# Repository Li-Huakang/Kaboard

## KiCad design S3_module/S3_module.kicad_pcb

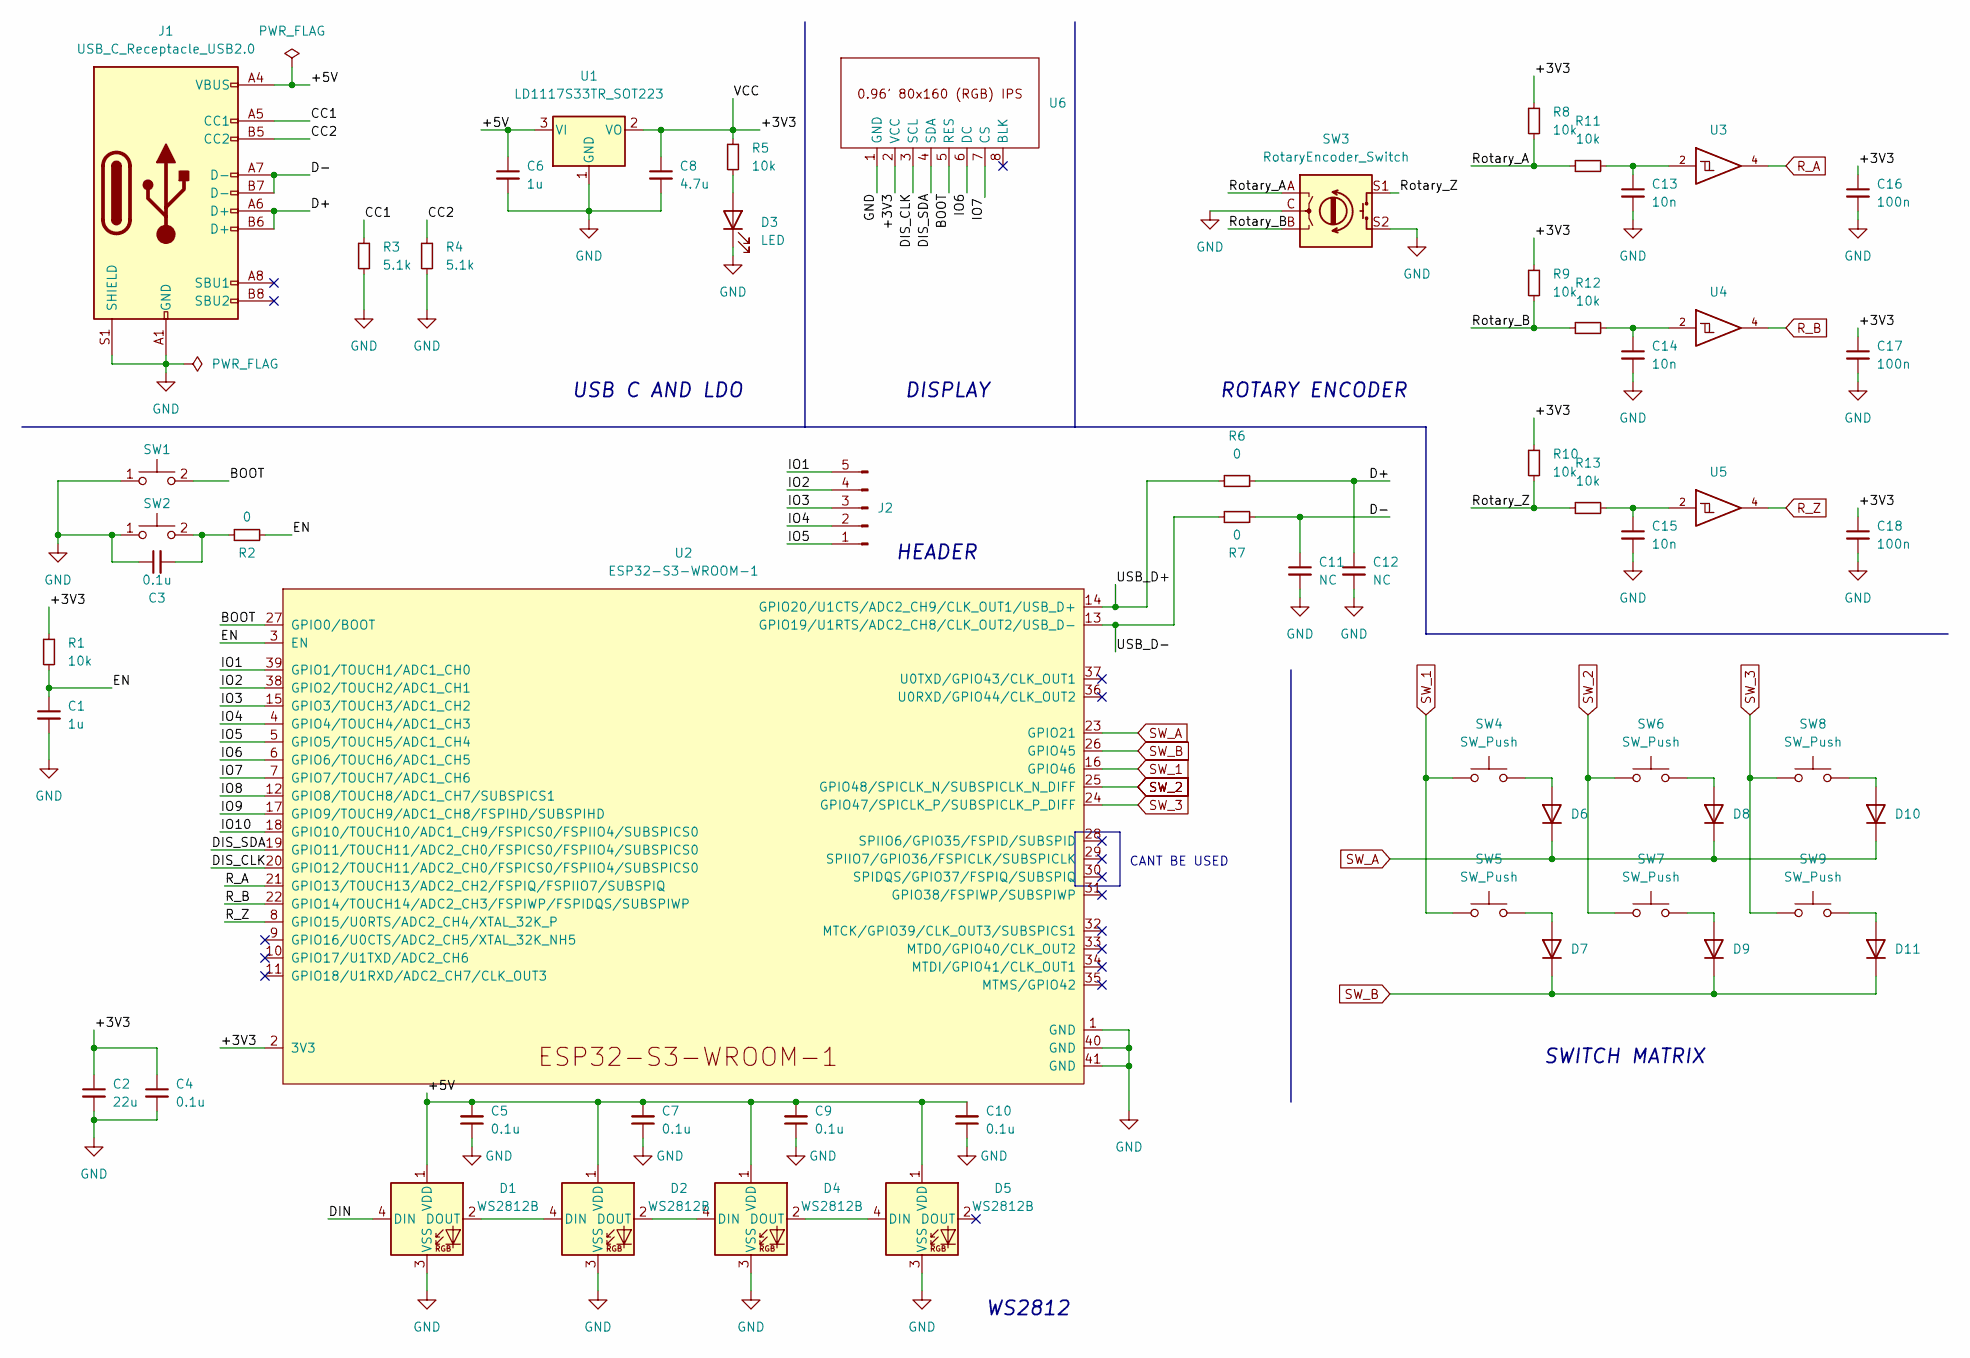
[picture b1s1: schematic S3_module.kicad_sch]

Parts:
C1, C6: 1u; C_0805_2012Metric_Pad1.18x1.45mm_HandSolder
C2: 22u; C_0805_2012Metric_Pad1.18x1.45mm_HandSolder
C3, C4, C5, C7, C9, C10: 0.1u; C_0805_2012Metric_Pad1.18x1.45mm_HandSolder
C8: 4.7u; C_0805_2012Metric_Pad1.18x1.45mm_HandSolder
C11, C12: NC; C_0805_2012Metric_Pad1.18x1.45mm_HandSolder
C13, C14, C15: 10n; C_0805_2012Metric_Pad1.18x1.45mm_HandSolder
C16, C17, C18: 100n; C_0805_2012Metric_Pad1.18x1.45mm_HandSolder
D1, D2, D4, D5: WS2812B; LED_WS2812B_PLCC4_5.0x5.0mm_P3.2mm
D3: LED; LED_0805_2012Metric_Pad1.15x1.40mm_HandSolder
D6, D7, D8, D9, D10, D11: 1N4148WS; D_SOD-323
J1: USB_C_Receptacle_USB2.0; USB_C_Receptacle_HRO_TYPE-C-31-M-12
J2: Conn_01x05_Male; PinHeader_1x05_P2.54mm_Vertical
R1, R5, R8, R9, R10, R11, R12, R13: 10k; R_0805_2012Metric_Pad1.20x1.40mm_HandSolder
R2, R6, R7: 0; R_0805_2012Metric_Pad1.20x1.40mm_HandSolder
R3, R4: 5.1k; R_0805_2012Metric_Pad1.20x1.40mm_HandSolder
SW1, SW2: (no value)
SW3: RotaryEncoder_Switch; RotaryEncoder_Alps_EC11E-Switch_Vertical_H20mm
SW4, SW5, SW6, SW7, SW8, SW9: SW_Push; SW_Cherry_MX_Plate_1.00u
U1: LD1117S33TR_SOT223; SOT-223-3_TabPin2
U2: ESP32-S3-WROOM-1
U3, U4, U5: 74LVC1G17; SOT-353_SC-70-5_Handsoldering
U6: 0.96_80x160_IPS

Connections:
/+5V: C5.2, C6.1, C7.2, C9.2, C10.2, D1.1 (VDD), D2.1 (VDD), D4.1 (VDD), D5.1 (VDD), J1.A4 (VBUS), J1.A9 (VBUS), J1.B4 (VBUS), J1.B9 (VBUS), U1.3 (VI)
/BOOT: SW1.2, U2.27 (GPIO0/BOOT), U6.5 (RES)
/CC1: J1.A5 (CC1), R3.1
/CC2: J1.B5 (CC2), R4.1
/D+: C12.1, J1.A6 (D+), J1.B6 (D+), R6.1
/D-: C11.1, J1.A7 (D-), J1.B7 (D-), R7.1
/DIN: D1.4 (DIN)
/DIS_CLK: U2.20 (GPIO12/TOUCH11/ADC2_CH0/FSPICS0/FSPIIO4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), U6.3 (SCL)
/DIS_SDA: U2.19 (GPIO11/TOUCH11/ADC2_CH0/FSPICS0/FSPIIO4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), U6.4 (SDA)
/EN: C1.1, R1.2, R2.2, U2.3 (EN)
/IO1: J2.5, U2.39 (GPIO1/TOUCH1/ADC1_CH0)
/IO2: J2.4, U2.38 (GPIO2/TOUCH2/ADC1_CH1)
/IO3: J2.3, U2.15 (GPIO3/TOUCH3/ADC1_CH2)
/IO4: J2.2, U2.4 (GPIO4/TOUCH4/ADC1_CH3)
/IO5: J2.1, U2.5 (GPIO5/TOUCH5/ADC1_CH4)
/IO6: U2.6 (GPIO6/TOUCH6/ADC1_CH5), U6.6 (DC)
/IO7: U2.7 (GPIO7/TOUCH7/ADC1_CH6), U6.7 (CS)
/IO8: U2.12 (GPIO8/TOUCH8/ADC1_CH7/SUBSPICS1)
/IO9: U2.17 (GPIO9/TOUCH9/ADC1_CH8/FSPIHD/SUBSPIHD)
/IO10: U2.18 (GPIO10/TOUCH10/ADC1_CH9/FSPICS0/FSPIIO4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)
/Rotary_A: R8.2, R11.1, SW3.A
/Rotary_B: R9.2, R12.1, SW3.B
/Rotary_Z: R10.2, R13.1, SW3.S1
/USB_D+: R6.2, U2.14 (GPIO20/U1CTS/ADC2_CH9/CLK_OUT1/USB_D+)
/USB_D-: R7.2, U2.13 (GPIO19/U1RTS/ADC2_CH8/CLK_OUT2/USB_D-)
GND: C1.2, C2.2, C3.1, C4.2, C5.1, C6.2, C7.1, C8.2, C9.1, C10.1, C11.2, C12.2, C13.2, C14.2, C15.2, C16.2, C17.2, C18.2, D1.3 (VSS), D2.3 (VSS), D3.1 (K), D4.3 (VSS), D5.3 (VSS), J1.A1 (GND), J1.A12 (GND), J1.B1 (GND), J1.B12 (GND), J1.S1 (SHIELD), R3.2, R4.2, SW1.1, SW2.1, SW3.C, SW3.S2, U1.1 (GND), U2.1 (GND), U2.40 (GND), U2.41 (GND), U3.3 (GND), U4.3 (GND), U5.3 (GND), U6.1 (GND)
unnamed: C3.2, R2.1, SW2.2
unnamed: C13.1, R11.2, U3.2
unnamed: C14.1, R12.2, U4.2
unnamed: C15.1, R13.2, U5.2
unnamed: D1.2 (DOUT), D2.4 (DIN)
unnamed: D2.2 (DOUT), D4.4 (DIN)
unnamed: D3.2 (A), R5.2
unnamed: D4.2 (DOUT), D5.4 (DIN)
unnamed: D6.2 (A), SW4.2
unnamed: D7.2 (A), SW5.2
unnamed: D8.2 (A), SW6.2
unnamed: D9.2 (A), SW7.2
unnamed: D10.2 (A), SW8.2
unnamed: D11.2 (A), SW9.2
R_A: U2.21 (GPIO13/TOUCH13/ADC2_CH2/FSPIQ/FSPIIO7/S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), U3.4
R_B: U2.22 (GPIO14/TOUCH14/ADC2_CH3/FSPIWP/FSPIDQS/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), U4.4
R_Z: U2.8 (GPIO15/U0RTS/ADC2_CH4/XTAL_32K_P), U5.4
SW_1: SW4.1, SW5.1, U2.16 (GPIO46)
SW_2: SW6.1, SW7.1, U2.25 (GPIO48/SPICLK_N/SUBSPICLK_N_DIFF)
SW_3: SW8.1, SW9.1, U2.24 (GPIO47/SPICLK_P/SUBSPICLK_P_DIFF)
SW_A: D6.1 (K), D8.1 (K), D10.1 (K), U2.23 (GPIO21)
SW_B: D7.1 (K), D9.1 (K), D11.1 (K), U2.26 (GPIO45)
VCC: C2.1, C4.1, C8.1, C16.1, C17.1, C18.1, R1.1, R5.1, R8.1, R9.1, R10.1, U1.2 (VO), U2.2 (3V3), U3.5 (VCC), U4.5 (VCC), U5.5 (VCC), U6.2 (VCC)

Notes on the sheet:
CANT BE USED
SWITCH MATRIX
USB C AND LDO
ROTARY ENCODER
DISPLAY
HEADER
WS2812

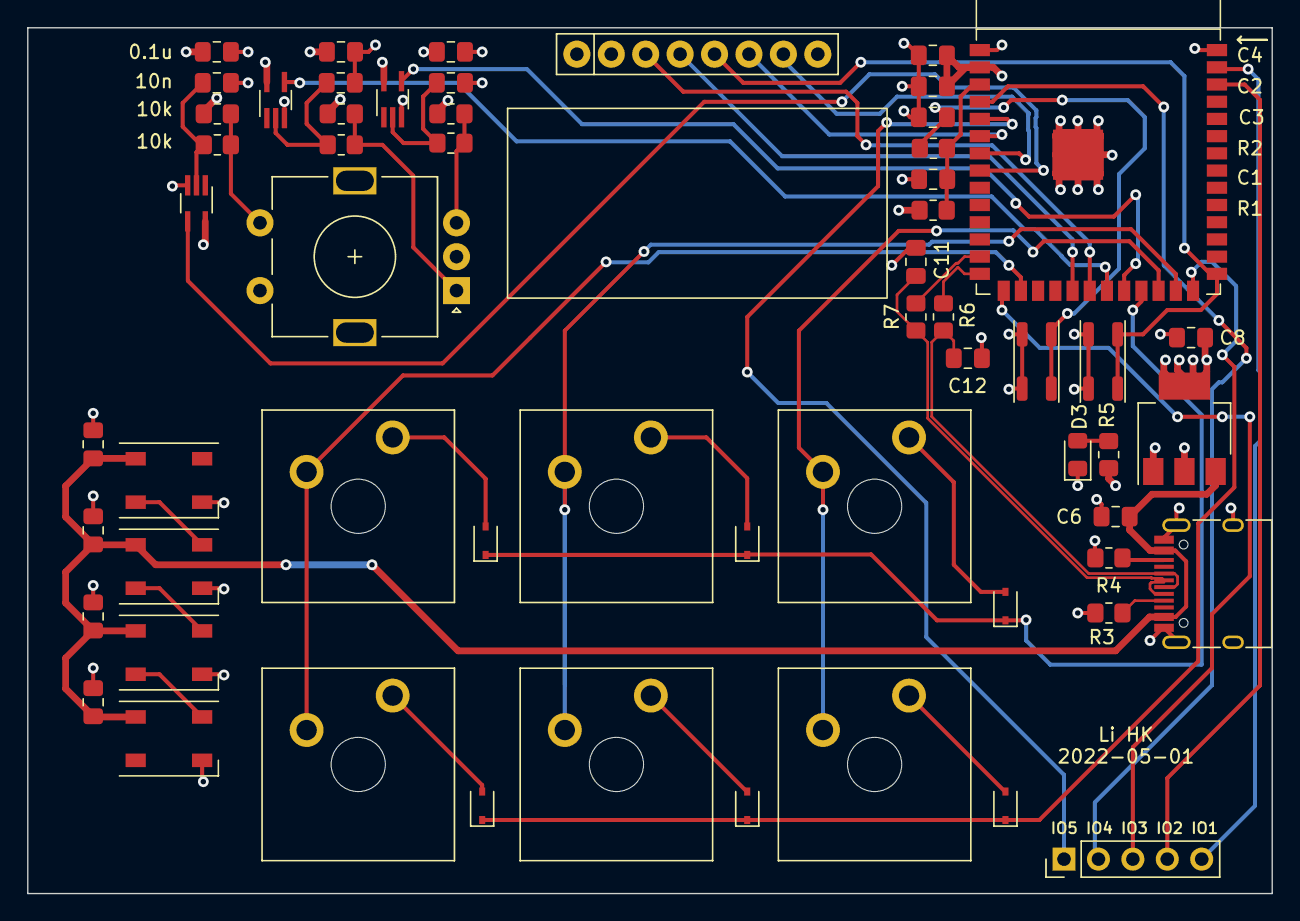
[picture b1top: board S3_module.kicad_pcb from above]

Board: 4 copper layers, 91.8 x 63.9 mm, 59 parts (0 on the bottom side), 45 nets.

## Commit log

2022-04-24 creat the project
2022-04-24 add rotary
2022-04-25 add power
2022-04-26 add footprint
2022-04-29 layout
2022-04-30 restore backup
2022-04-30 route, to be revise
2022-05-10 last version
